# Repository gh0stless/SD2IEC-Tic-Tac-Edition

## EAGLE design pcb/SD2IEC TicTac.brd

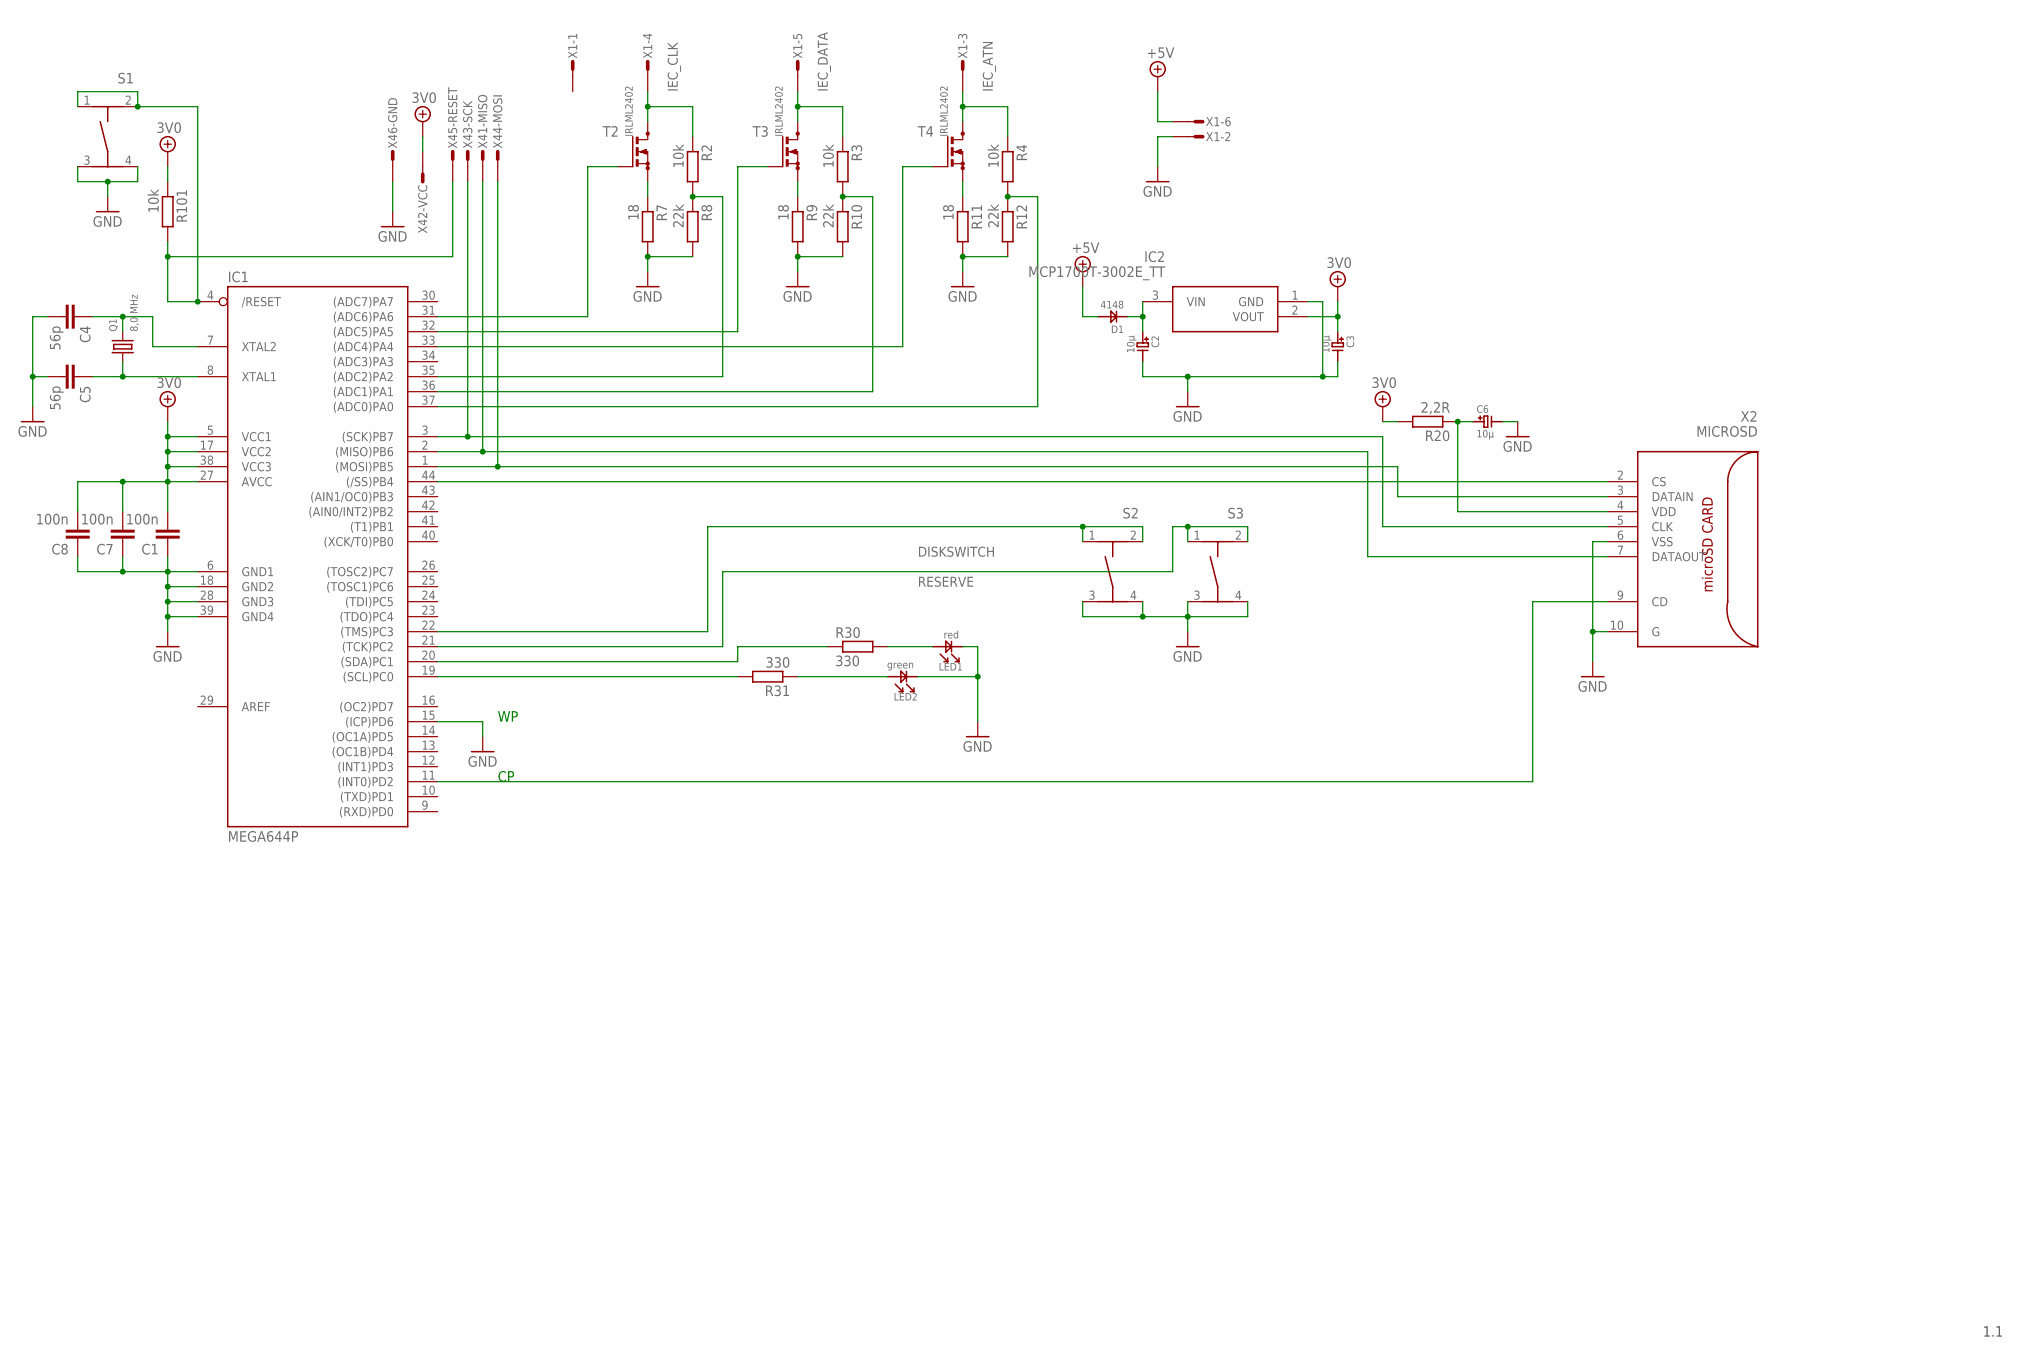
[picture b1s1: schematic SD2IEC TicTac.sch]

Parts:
C1, C7, C8: 100n; C0805K
C2, C3, C6: 10µ; C_TANTAL_A
C4, C5: 56p; C0805K
D1: 4148; SOD-123
IC1: MEGA644P; TQFP44
IC2: MCP1700T-3002E_TT; SOT95P237X112-3N
LED1: red; LED1206
LED2: green; LED1206
Q1: 8,0 MHz; HC49/S
R2, R3, R4, R101: 10k; R0805
R7, R9, R11: 18; R0805
R8, R10, R12: 22k; R0805
R20: 2,2R; R0805
R30, R31: 330; R0805
S1, S2, S3: TASTER-9314_SMD
T2, T3, T4: IRLML2402; SOT23_C
X1: MICROMATCH-6_PIN; MICROMATCH-6
X2: MICROSD; MICRO_SD_CONNECTOR
X4: AVR-ISP_1X6; 1X6_ISP

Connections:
3V0: C1.2, C3.1, C7.2, C8.2, IC1.5 (VCC1), IC1.17 (VCC2), IC1.27 (AVCC), IC1.38 (VCC3), IC2.2 (VOUT), R20.2, R101.1, X4.2
+5V: D1.2, X1.6
/RESET: IC1.4 (/RESET), R101.2, S1.1, S1.2, X4.5
ATN: IC1.37 ((ADC0)PA0), R4.2, R12.1
CLK: IC1.35 ((ADC2)PA2), R2.2, R8.1
DATA: IC1.36 ((ADC1)PA1), R3.2, R10.1
DISKSWITCH: IC1.22 ((TMS)PC3), S2.1, S2.2
GND: C1.1, C2.2, C3.2, C4.2, C5.2, C6.2, C7.1, C8.1, IC1.6 (GND1), IC1.15 ((ICP)PD6), IC1.18 (GND2), IC1.28 (GND3), IC1.39 (GND4), IC2.1 (GND), LED1.1, LED2.1, R7.2, R8.2, R9.2, R10.2, R11.2, R12.2, S1.3, S1.4, S2.3, S2.4, S3.3, S3.4, X1.2, X2.6 (VSS), X2.10 (G), X4.6
IEC_ATN: R4.1, T4.3 (D), X1.3
IEC_CLK: R2.1, T2.3 (D), X1.4
IEC_DATA: R3.1, T3.3 (D), X1.5
LED2: LED2.2, R31.1
MISO: IC1.2 ((MISO)PB6), X2.7 (DATAOUT), X4.1
MOSI: IC1.1 ((MOSI)PB5), X2.3 (DATAIN), X4.4
unnamed: LED1.2, R30.2
unnamed: C2.1, D1.1, IC2.3 (VIN)
unnamed: C5.1, IC1.8 (XTAL1), Q1.1
unnamed: C4.1, IC1.7 (XTAL2), Q1.2
unnamed: C6.1, R20.1, X2.4 (VDD)
unnamed: IC1.11 ((INT0)PD2), X2.9 (CD)
unnamed: IC1.32 ((ADC5)PA5), T3.1 (G)
unnamed: IC1.33 ((ADC4)PA4), T4.1 (G)
unnamed: IC1.31 ((ADC6)PA6), T2.1 (G)
unnamed: R7.1, T2.2 (S)
unnamed: R9.1, T3.2 (S)
unnamed: R11.1, T4.2 (S)
PC0: IC1.19 ((SCL)PC0), R31.2
PC1: IC1.20 ((SDA)PC1), R30.1
RESERVE: IC1.21 ((TCK)PC2), S3.1, S3.2
SCK: IC1.3 ((SCK)PB7), X2.5 (CLK), X4.3
SS: IC1.44 ((/SS)PB4), X2.2 (CS)

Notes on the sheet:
1.1

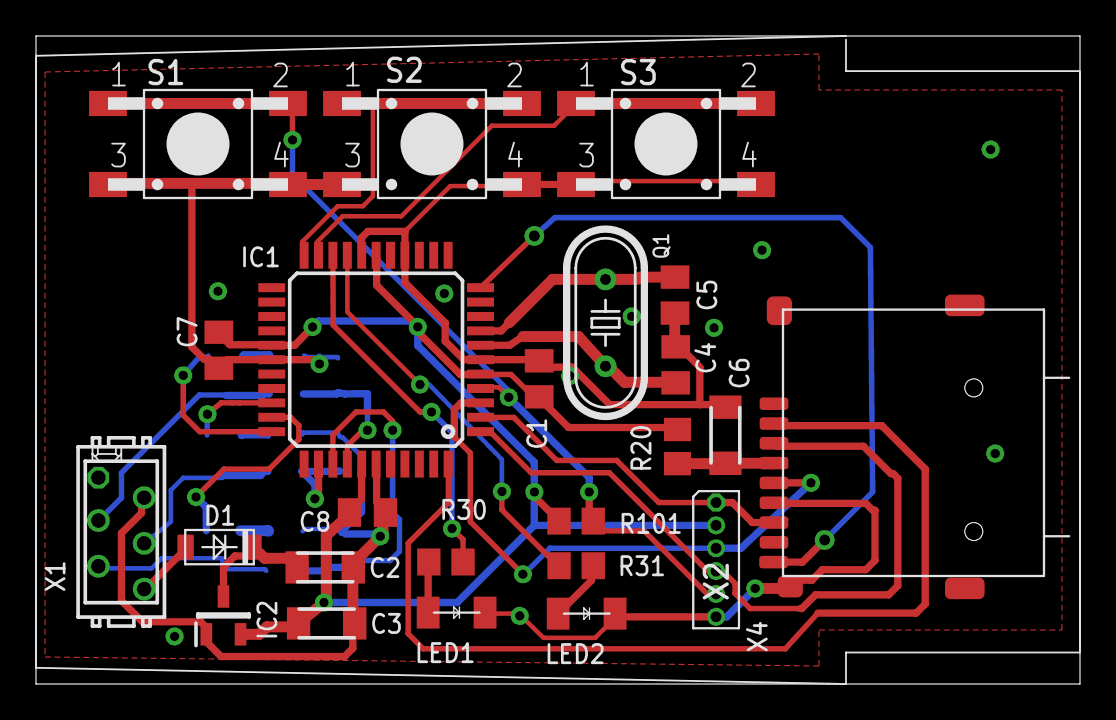
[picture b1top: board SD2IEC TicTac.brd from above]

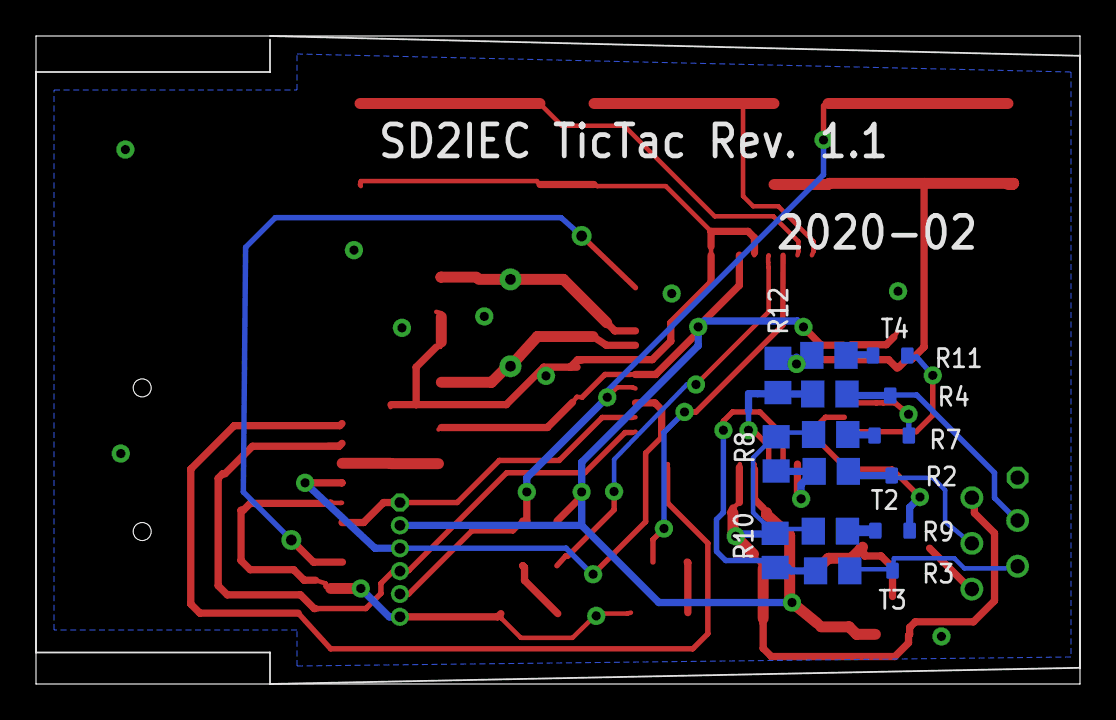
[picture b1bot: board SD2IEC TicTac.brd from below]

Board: 2 copper layers, 58.0 x 36.0 mm, 36 parts (12 on the bottom side), 31 nets.

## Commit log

2023-07-09 init
2023-07-30 firmware update
2023-08-02 some changes
2023-08-02 einige Aenderungen
2023-08-02 Fehlerteufelchen
2023-08-02 move legacy
2023-08-02 edit BOM
2023-08-02 add pics
2023-08-02 Fehlerteufel
2023-08-03 add gerbers
2023-08-03 reorder
2023-08-03 add pic
2023-08-03 Aufbauanleitung zugefügt
2023-08-03 finish
2023-08-29 updated Spickzettel
